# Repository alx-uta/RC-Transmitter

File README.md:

# RC-Transmitter
This is a custom RC Transmitter that's using ESP32 and Semtech SX1280

Authors:
- Marian Uta
- Alex Heisler

# Project Status - WIP
- [https://microknot.dev/rc-transmitter-project-status/](https://microknot.dev/rc-transmitter-project-status/)

---

# Useful links
- [Build Tutorial](https://microknot.dev/rc-transmitter-build-tutorial-esp32-sx1280/)
- [Wiring Tutorial](https://microknot.dev/rc-transmitter-wiring-tutorial-esp32-sx1280/)
- [Calibration Tutorial](https://microknot.dev/rc-transmitter-calibration-tutorial/)

---

- Required Parts:
  - [3D Files](https://docs.google.com/spreadsheets/d/1K6EamDLu7aNF5GFfuzi9vV8SCz_6HzOA_h1CgVDcLqo/edit?usp=sharing)
  - [PCB](https://docs.google.com/spreadsheets/d/1bTyJoKmJrHec9gnfRhsfcdIJgJ4cUt9kbDGZgcYngUU/edit?usp=sharing)
  - [BOM](https://docs.google.com/spreadsheets/d/1osKjM83mz0m_O5QN-AISYl1IssTSeUwu/edit?usp=sharing&ouid=117182597298978401444&rtpof=true&sd=true)

---
Links:
- [Discord](https://discord.gg/eHyz2aJ6)

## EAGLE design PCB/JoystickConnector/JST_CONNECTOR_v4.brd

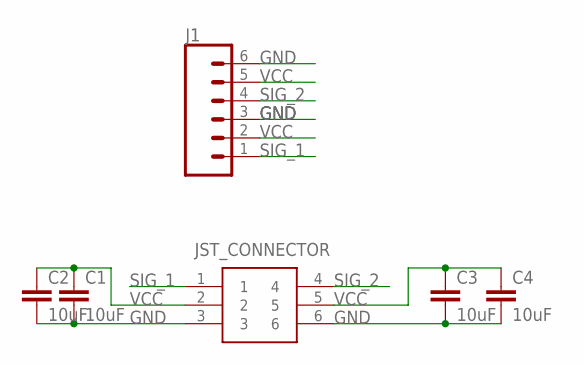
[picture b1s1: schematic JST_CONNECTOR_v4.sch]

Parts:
C1, C2, C3, C4: 10uF; 0805
J1: CONN_06SILK_FEMALE_PTH; 1X06
JST_CONNECTOR: 0532610671

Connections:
GND: C1.2, C2.2, C3.2, C4.2, J1.3, J1.6, JST_CONNECTOR.3, JST_CONNECTOR.6
SIG_1: J1.1, JST_CONNECTOR.1
SIG_2: J1.4, JST_CONNECTOR.4
VCC: C1.1, C2.1, C3.1, C4.1, J1.2, J1.5, JST_CONNECTOR.2, JST_CONNECTOR.5

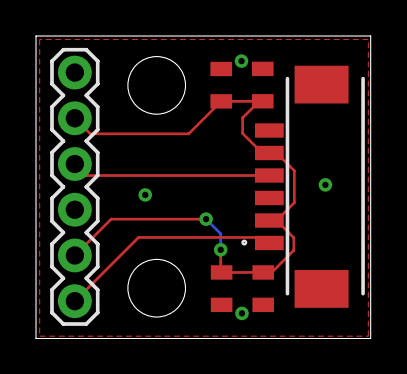
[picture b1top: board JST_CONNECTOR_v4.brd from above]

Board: 2 copper layers, 18.6 x 16.8 mm, 6 parts (0 on the bottom side), 4 nets.

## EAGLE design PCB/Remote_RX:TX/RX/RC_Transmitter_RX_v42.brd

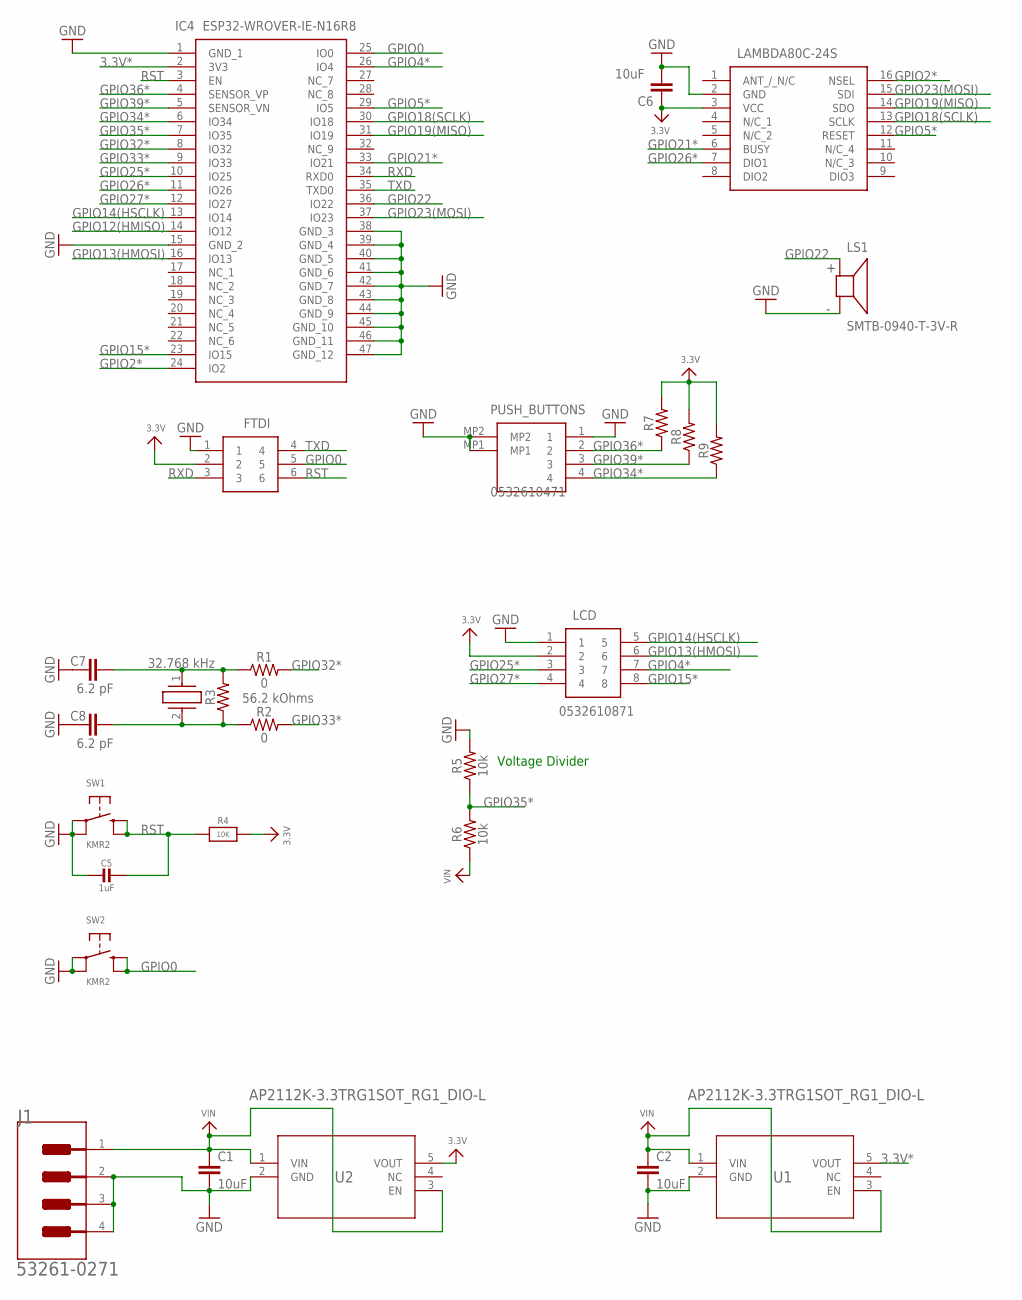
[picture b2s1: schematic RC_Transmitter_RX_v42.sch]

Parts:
C1, C2, C6: 10uF; 0805
C5: 1uF; 0805-NO
C7, C8: 6.2 pF; CAPC2012X110
CRYSTAL: 32.768 kHz; ECX327CDX1293
FTDI: 0532610671
IC1: LAMBDA80C-24S; LAMBDA80C24S
IC4: ESP32-WROVER-IE-N16R8; ESP32WROVERIEN16R8
J1: MOLEX_53261-0271MOLEX_53261-0271_0_0; MOLEX_53261-0271_0
LCD: 0532610871; 53261-0871
LS1: SMTB-0940-T-3V-R; XDCR_SMTB-0940-T-3V-R
PUSH_BUTTONS: 0532610471
R1, R2, R7, R8, R9: 0; 0603
R3: 56.2 kOhms; 0603
R4: 10K; _0805
R5, R6: 10k; 0603
SW1, SW2: KMR2; BTN_KMR2_4.6X2.8
U1, U2: AP2112K-3.3TRG1SOT_RG1_DIO-L; SOT_RG1_DIO-L

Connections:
3.3V: C6.1, FTDI.2, IC1.3 (VCC), LCD.2, R4.2, R7.2, R8.2, R9.2, U2.5 (VOUT)
3.3V*: IC4.2 (3V3), U1.5 (VOUT)
GND: C1.2, C2.2, C5.2, C6.2, C7.1, C8.1, FTDI.1, IC1.2 (GND), IC4.1 (GND_1), IC4.15 (GND_2), IC4.38 (GND_3), IC4.39 (GND_4), IC4.40 (GND_5), IC4.41 (GND_6), IC4.42 (GND_7), IC4.43 (GND_8), IC4.44 (GND_9), IC4.45 (GND_10), IC4.46 (GND_11), IC4.47 (GND_12), J1.2, J1.3 (MNT_1), J1.4 (MNT_2), LCD.1, LS1.N, PUSH_BUTTONS.1, PUSH_BUTTONS.MP1, PUSH_BUTTONS.MP2, R5.2, SW1.A, SW1.A' (P1), SW2.A, SW2.A' (P1), U1.2 (GND), U2.2 (GND)
GPIO0: FTDI.5, IC4.25 (IO0), SW2.B (S), SW2.B' (S1)
GPIO2*: IC1.16 (NSEL), IC4.24 (IO2)
GPIO4*: IC4.26 (IO4), LCD.7
GPIO5*: IC1.12 (RESET), IC4.29 (IO5)
GPIO12(HMISO): IC4.14 (IO12)
GPIO13(HMOSI): IC4.16 (IO13), LCD.6
GPIO14(HSCLK): IC4.13 (IO14), LCD.5
GPIO15*: IC4.23 (IO15), LCD.8
GPIO18(SCLK): IC1.13 (SCLK), IC4.30 (IO18)
GPIO19(MISO): IC1.14 (SDO), IC4.31 (IO19)
GPIO21*: IC1.6 (BUSY), IC4.33 (IO21)
GPIO22: IC4.36 (IO22), LS1.P
GPIO23(MOSI): IC1.15 (SDI), IC4.37 (IO23)
GPIO25*: IC4.10 (IO25), LCD.3
GPIO26*: IC1.7 (DIO1), IC4.11 (IO26)
GPIO27*: IC4.12 (IO27), LCD.4
GPIO32*: IC4.8 (IO32), R1.2
GPIO33*: IC4.9 (IO33), R2.2
GPIO34*: IC4.6 (IO34), PUSH_BUTTONS.4, R9.1
GPIO35*: IC4.7 (IO35), R5.1, R6.2
GPIO36*: IC4.4 (SENSOR_VP), PUSH_BUTTONS.2, R7.1
GPIO39*: IC4.5 (SENSOR_VN), PUSH_BUTTONS.3, R8.1
unnamed: C7.2, CRYSTAL.1 (X1), R1.1, R3.2
unnamed: C8.2, CRYSTAL.2 (X2), R2.1, R3.1
RST: C5.1, FTDI.6, IC4.3 (EN), R4.1, SW1.B (S), SW1.B' (S1)
RXD: FTDI.3, IC4.34 (RXD0)
TXD: FTDI.4, IC4.35 (TXD0)
VIN: C1.1, C2.1, J1.1, R6.1, U1.1 (VIN), U1.3 (EN), U2.1 (VIN), U2.3 (EN)

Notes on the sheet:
Voltage Divider

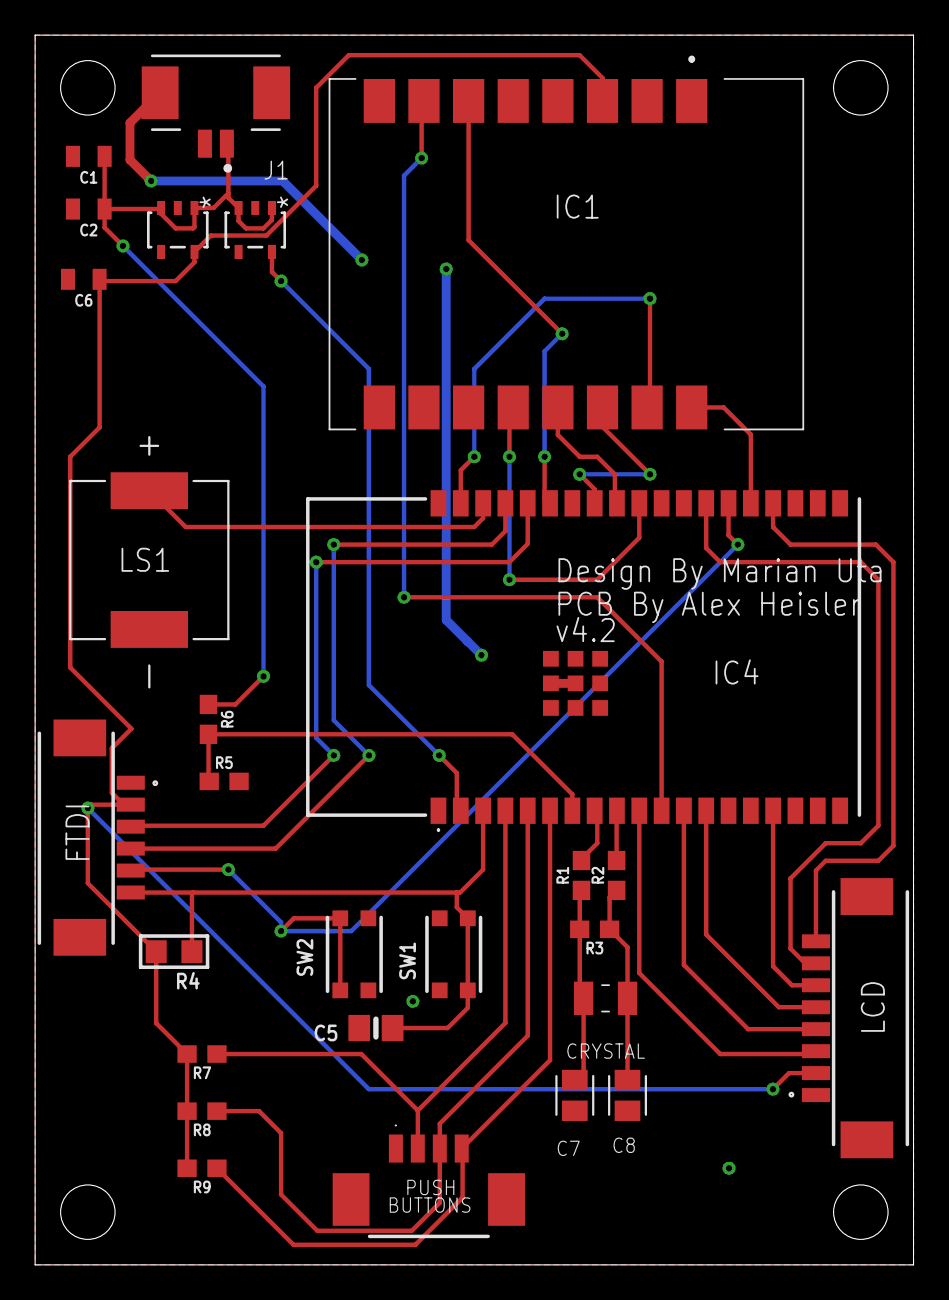
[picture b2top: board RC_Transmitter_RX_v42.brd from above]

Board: 2 copper layers, 50.0 x 70.0 mm, 27 parts (0 on the bottom side), 30 nets.

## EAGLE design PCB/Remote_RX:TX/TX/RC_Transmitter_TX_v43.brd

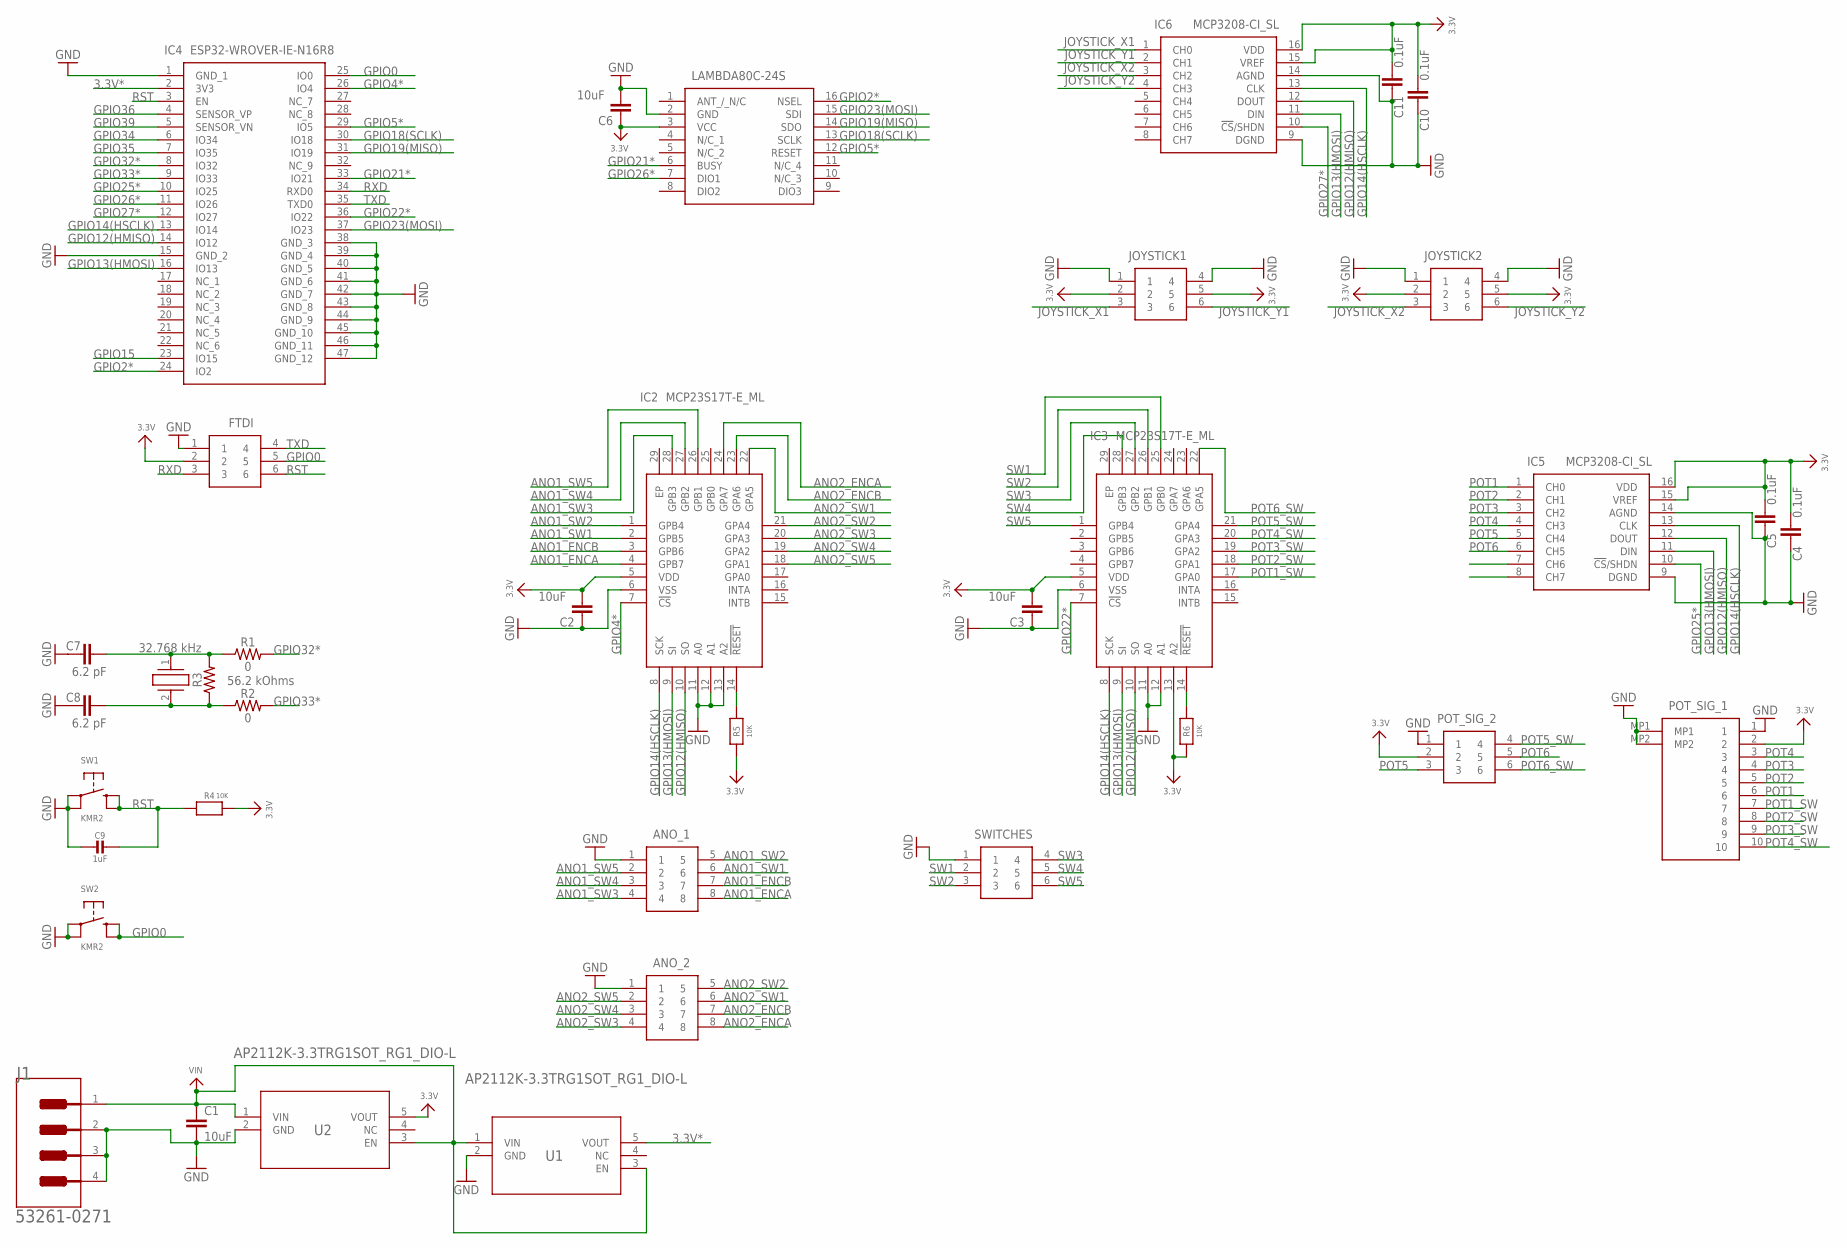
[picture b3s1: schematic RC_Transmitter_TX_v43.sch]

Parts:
ANO_1, ANO_2: 0532610871; 53261-0871
C1, C2, C3, C6: 10uF; 0805
C4, C5, C10, C11: 0.1uF; 0805
C7, C8: 6.2 pF; CAPC2012X110
C9: 1uF; 0805-NO
CRYSTAL: 32.768 kHz; ECX327CDX1293
FTDI: 0532610671
IC1: LAMBDA80C-24S; LAMBDA80C24S
IC2, IC3: MCP23S17T-E_ML; QFN65P600X600X100-29N
IC4: ESP32-WROVER-IE-N16R8; ESP32WROVERIEN16R8
IC5, IC6: MCP3208-CI_SL; SOIC127P600X175-16N
J1: MOLEX_53261-0271MOLEX_53261-0271_0_0; MOLEX_53261-0271_0
JOYSTICK1, JOYSTICK2: 0532610671
POT_SIG_1: 0532611071
POT_SIG_2: 0532610671
R1, R2: 0; 0603
R3: 56.2 kOhms; 0603
R4, R5, R6: 10K; _0805
SW1, SW2: KMR2; BTN_KMR2_4.6X2.8
SWITCHES: 0532610671
U1, U2: AP2112K-3.3TRG1SOT_RG1_DIO-L; SOT_RG1_DIO-L

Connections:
3.3V: C2.2, C3.2, C4.2, C5.2, C6.1, C10.2, C11.2, FTDI.2, IC1.3 (VCC), IC2.5 (VDD), IC3.5 (VDD), IC3.13 (A2), IC5.15 (VREF), IC5.16 (VDD), IC6.15 (VREF), IC6.16 (VDD), JOYSTICK1.2, JOYSTICK1.5, JOYSTICK2.2, JOYSTICK2.5, POT_SIG_1.2, POT_SIG_2.2, R4.2, R5.1, R6.1, U2.5 (VOUT)
3.3V*: IC4.2 (3V3), U1.5 (VOUT)
ANO1_ENCA: ANO_1.8, IC2.4 (GPB7)
ANO1_ENCB: ANO_1.7, IC2.3 (GPB6)
ANO1_SW1: ANO_1.6, IC2.2 (GPB5)
ANO1_SW2: ANO_1.5, IC2.1 (GPB4)
ANO1_SW3: ANO_1.4, IC2.28 (GPB3)
ANO1_SW4: ANO_1.3, IC2.27 (GPB2)
ANO1_SW5: ANO_1.2, IC2.26 (GPB1)
ANO2_ENCA: ANO_2.8, IC2.24 (GPA7)
ANO2_ENCB: ANO_2.7, IC2.23 (GPA6)
ANO2_SW1: ANO_2.6, IC2.22 (GPA5)
ANO2_SW2: ANO_2.5, IC2.21 (GPA4)
ANO2_SW3: ANO_2.4, IC2.20 (GPA3)
ANO2_SW4: ANO_2.3, IC2.19 (GPA2)
ANO2_SW5: ANO_2.2, IC2.18 (GPA1)
GND: ANO_1.1, ANO_2.1, C1.2, C2.1, C3.1, C4.1, C5.1, C6.2, C7.1, C8.1, C9.2, C10.1, C11.1, FTDI.1, IC1.2 (GND), IC2.6 (VSS), IC2.11 (A0), IC2.12 (A1), IC2.13 (A2), IC3.6 (VSS), IC3.11 (A0), IC3.12 (A1), IC4.1 (GND_1), IC4.15 (GND_2), IC4.38 (GND_3), IC4.39 (GND_4), IC4.40 (GND_5), IC4.41 (GND_6), IC4.42 (GND_7), IC4.43 (GND_8), IC4.44 (GND_9), IC4.45 (GND_10), IC4.46 (GND_11), IC4.47 (GND_12), IC5.9 (DGND), IC5.14 (AGND), IC6.9 (DGND), IC6.14 (AGND), J1.2, J1.3 (MNT_1), J1.4 (MNT_2), JOYSTICK1.1, JOYSTICK1.4, JOYSTICK2.1, JOYSTICK2.4, POT_SIG_1.1, POT_SIG_1.MP1, POT_SIG_1.MP2, POT_SIG_2.1, SW1.A, SW1.A' (P1), SW2.A, SW2.A' (P1), SWITCHES.1, U1.2 (GND), U2.2 (GND)
GPIO0: FTDI.5, IC4.25 (IO0), SW2.B (S), SW2.B' (S1)
GPIO2*: IC1.16 (NSEL), IC4.24 (IO2)
GPIO4*: IC2.7 (!CS), IC4.26 (IO4)
GPIO5*: IC1.12 (RESET), IC4.29 (IO5)
GPIO12(HMISO): IC2.10 (SO), IC3.10 (SO), IC4.14 (IO12), IC5.12 (DOUT), IC6.12 (DOUT)
GPIO13(HMOSI): IC2.9 (SI), IC3.9 (SI), IC4.16 (IO13), IC5.11 (DIN), IC6.11 (DIN)
GPIO14(HSCLK): IC2.8 (SCK), IC3.8 (SCK), IC4.13 (IO14), IC5.13 (CLK), IC6.13 (CLK)
GPIO15: IC4.23 (IO15)
GPIO18(SCLK): IC1.13 (SCLK), IC4.30 (IO18)
GPIO19(MISO): IC1.14 (SDO), IC4.31 (IO19)
GPIO21*: IC1.6 (BUSY), IC4.33 (IO21)
GPIO22*: IC3.7 (!CS), IC4.36 (IO22)
GPIO23(MOSI): IC1.15 (SDI), IC4.37 (IO23)
GPIO25*: IC4.10 (IO25), IC5.10 (!CS!/SHDN)
GPIO26*: IC1.7 (DIO1), IC4.11 (IO26)
GPIO27*: IC4.12 (IO27), IC6.10 (!CS!/SHDN)
GPIO32*: IC4.8 (IO32), R1.2
GPIO33*: IC4.9 (IO33), R2.2
GPIO34: IC4.6 (IO34)
GPIO35: IC4.7 (IO35)
GPIO36: IC4.4 (SENSOR_VP)
GPIO39: IC4.5 (SENSOR_VN)
JOYSTICK_X1: IC6.1 (CH0), JOYSTICK1.3
JOYSTICK_X2: IC6.3 (CH2), JOYSTICK2.3
JOYSTICK_Y1: IC6.2 (CH1), JOYSTICK1.6
JOYSTICK_Y2: IC6.4 (CH3), JOYSTICK2.6
unnamed: C7.2, CRYSTAL.1 (X1), R1.1, R3.2
unnamed: C8.2, CRYSTAL.2 (X2), R2.1, R3.1
unnamed: IC2.14 (!RESET), R5.2
unnamed: IC3.14 (!RESET), R6.2
POT1: IC5.1 (CH0), POT_SIG_1.6
POT1_SW: IC3.17 (GPA0), POT_SIG_1.7
POT2: IC5.2 (CH1), POT_SIG_1.5
POT2_SW: IC3.18 (GPA1), POT_SIG_1.8
POT3: IC5.3 (CH2), POT_SIG_1.4
POT3_SW: IC3.19 (GPA2), POT_SIG_1.9
POT4: IC5.4 (CH3), POT_SIG_1.3
POT4_SW: IC3.20 (GPA3), POT_SIG_1.10
POT5: IC5.5 (CH4), POT_SIG_2.3
POT5_SW: IC3.21 (GPA4), POT_SIG_2.4
POT6: IC5.6 (CH5), POT_SIG_2.5
POT6_SW: IC3.22 (GPA5), POT_SIG_2.6
RST: C9.1, FTDI.6, IC4.3 (EN), R4.1, SW1.B (S), SW1.B' (S1)
RXD: FTDI.3, IC4.34 (RXD0)
SW1: IC3.25 (GPB0), SWITCHES.2
SW2: IC3.26 (GPB1), SWITCHES.3
SW3: IC3.27 (GPB2), SWITCHES.4
SW4: IC3.28 (GPB3), SWITCHES.5
SW5: IC3.1 (GPB4), SWITCHES.6
TXD: FTDI.4, IC4.35 (TXD0)
VIN: C1.1, J1.1, U1.1 (VIN), U1.3 (EN), U2.1 (VIN), U2.3 (EN)

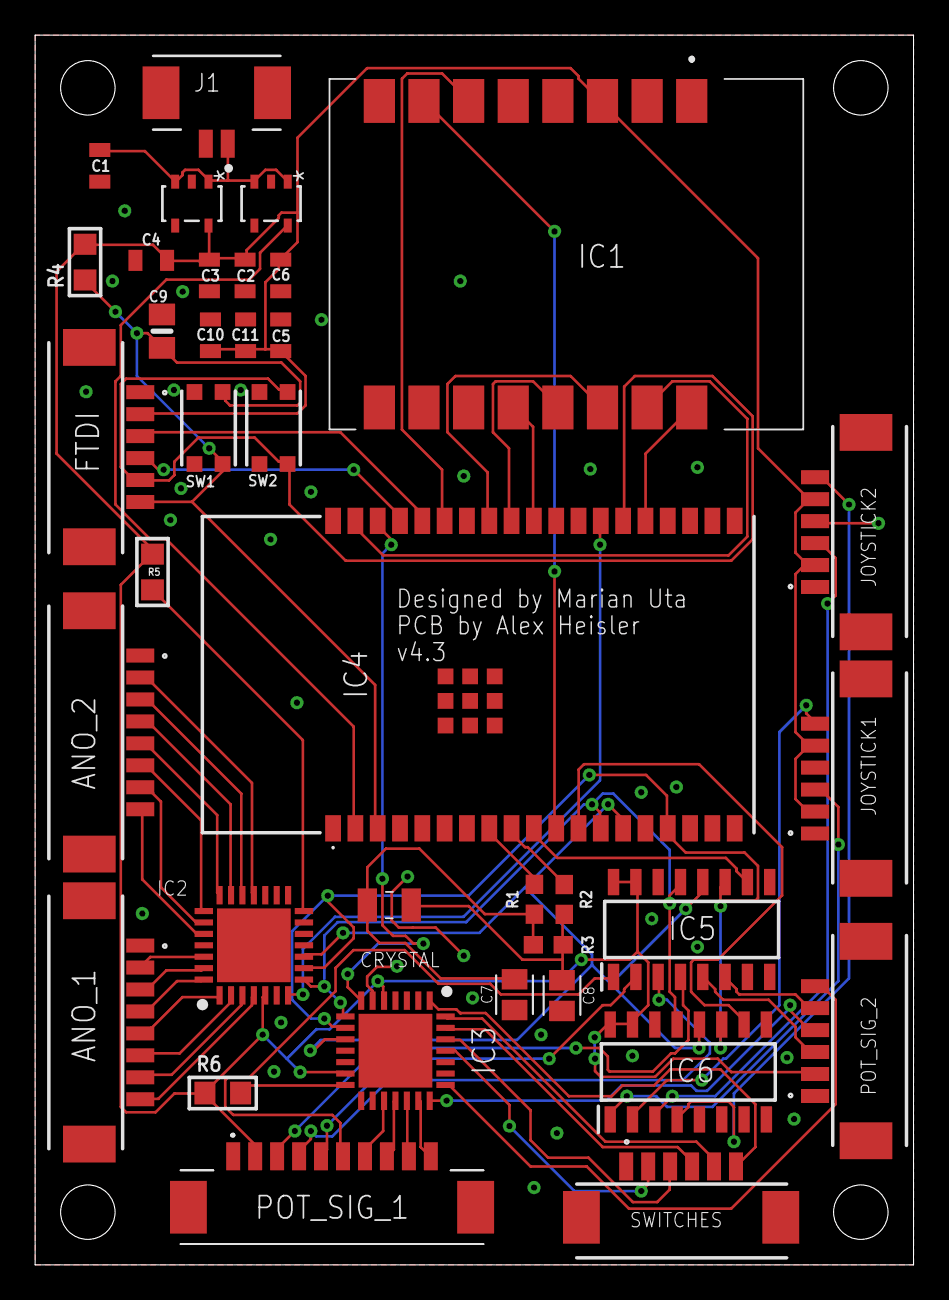
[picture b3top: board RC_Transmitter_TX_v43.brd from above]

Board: 2 copper layers, 50.0 x 70.0 mm, 37 parts (0 on the bottom side), 63 nets.

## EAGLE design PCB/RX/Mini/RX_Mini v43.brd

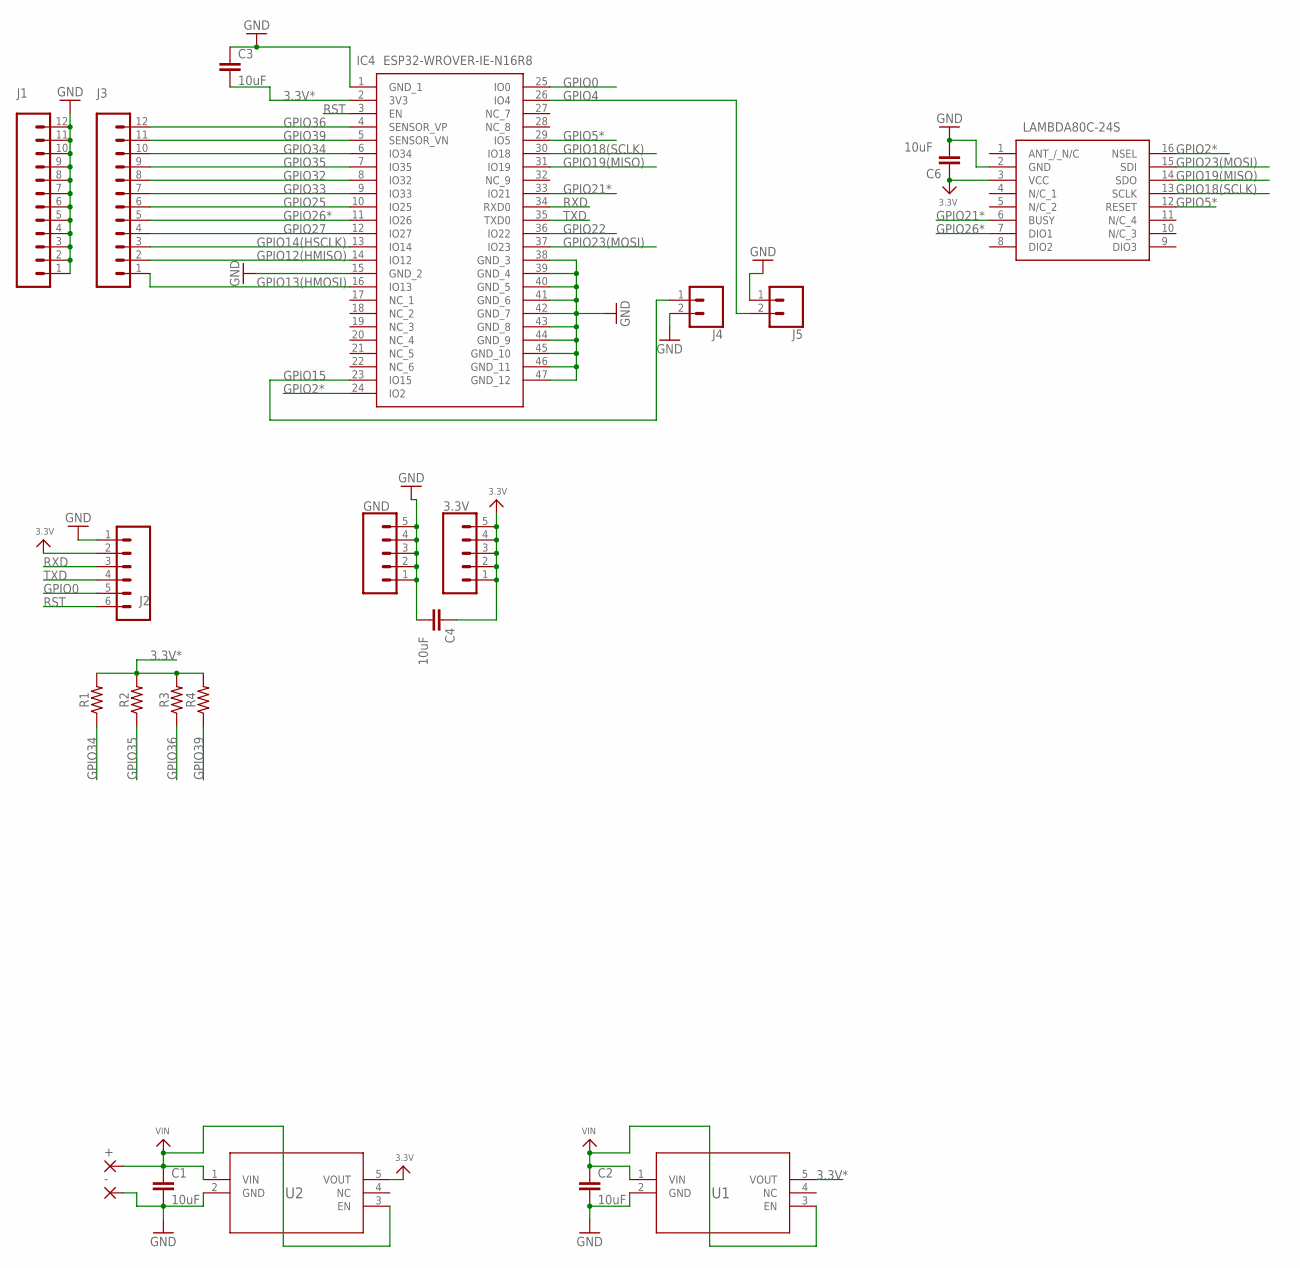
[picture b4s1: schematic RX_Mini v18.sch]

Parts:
3.3V: CONN_05; 1X05
+: 2,15/1,0
-: 2,15/1,0
C1, C2, C3, C4, C6: 10uF; 0805
GND: CONN_05; 1X05
IC1: LAMBDA80C-24S; LAMBDA80C24S
IC4: ESP32-WROVER-IE-N16R8; ESP32WROVERIEN16R8
J1, J3: CONN_12; 1X12
J2: CONN_06NO_SILK_NO_POP; 1X06_NO_SILK
J4, J5: CONN_02; 1X02
R1, R2, R3, R4: 0; 0603
U1, U2: AP2112K-3.3TRG1SOT_RG1_DIO-L; SOT_RG1_DIO-L

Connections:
3.3V: 3.3V.1, 3.3V.2, 3.3V.3, 3.3V.4, 3.3V.5, C4.1, C6.1, IC1.3 (VCC), J2.2, U2.5 (VOUT)
3.3V*: C3.2, IC4.2 (3V3), R1.2, R2.2, R3.2, R4.2, U1.5 (VOUT)
GND: -.1, C1.2, C2.2, C3.1, C4.2, C6.2, GND.1, GND.2, GND.3, GND.4, GND.5, IC1.2 (GND), IC4.1 (GND_1), IC4.15 (GND_2), IC4.38 (GND_3), IC4.39 (GND_4), IC4.40 (GND_5), IC4.41 (GND_6), IC4.42 (GND_7), IC4.43 (GND_8), IC4.44 (GND_9), IC4.45 (GND_10), IC4.46 (GND_11), IC4.47 (GND_12), J1.1, J1.2, J1.3, J1.4, J1.5, J1.6, J1.7, J1.8, J1.9, J1.10, J1.11, J1.12, J2.1, J4.2, J5.1, U1.2 (GND), U2.2 (GND)
GPIO0: IC4.25 (IO0), J2.5
GPIO2*: IC1.16 (NSEL), IC4.24 (IO2)
GPIO4: IC4.26 (IO4), J5.2
GPIO5*: IC1.12 (RESET), IC4.29 (IO5)
GPIO12(HMISO): IC4.14 (IO12), J3.2
GPIO13(HMOSI): IC4.16 (IO13), J3.1
GPIO14(HSCLK): IC4.13 (IO14), J3.3
GPIO15: IC4.23 (IO15), J4.1
GPIO18(SCLK): IC1.13 (SCLK), IC4.30 (IO18)
GPIO19(MISO): IC1.14 (SDO), IC4.31 (IO19)
GPIO21*: IC1.6 (BUSY), IC4.33 (IO21)
GPIO22: IC4.36 (IO22)
GPIO23(MOSI): IC1.15 (SDI), IC4.37 (IO23)
GPIO25: IC4.10 (IO25), J3.6
GPIO26*: IC1.7 (DIO1), IC4.11 (IO26), J3.5
GPIO27: IC4.12 (IO27), J3.4
GPIO32: IC4.8 (IO32), J3.8
GPIO33: IC4.9 (IO33), J3.7
GPIO34: IC4.6 (IO34), J3.10, R1.1
GPIO35: IC4.7 (IO35), J3.9, R2.1
GPIO36: IC4.4 (SENSOR_VP), J3.12, R3.1
GPIO39: IC4.5 (SENSOR_VN), J3.11, R4.1
RST: IC4.3 (EN), J2.6
RXD: IC4.34 (RXD0), J2.3
TXD: IC4.35 (TXD0), J2.4
VIN: +.1, C1.1, C2.1, U1.1 (VIN), U1.3 (EN), U2.1 (VIN), U2.3 (EN)

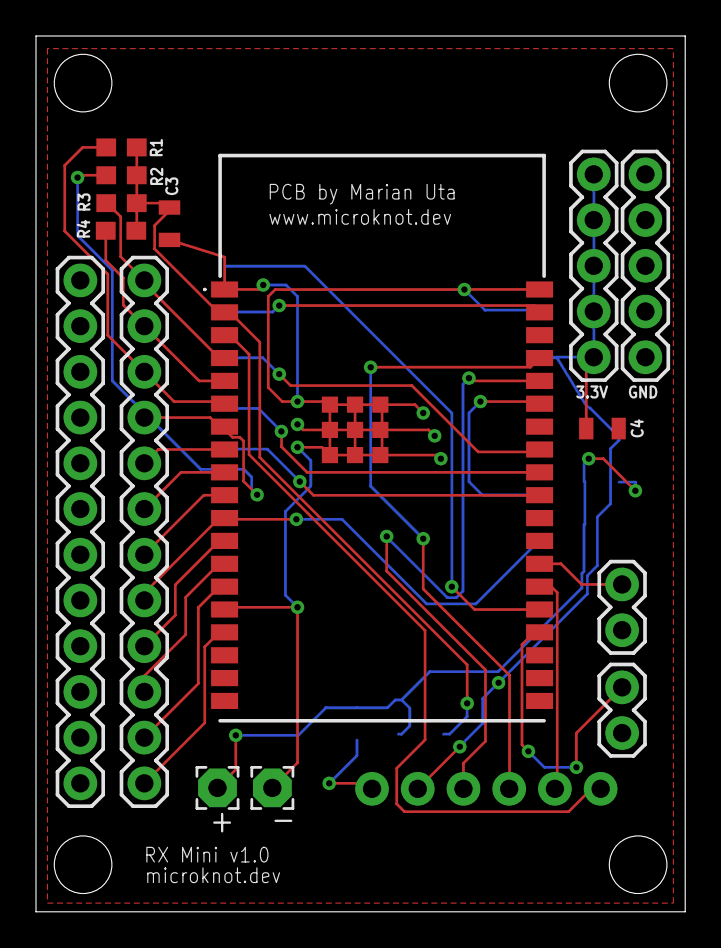
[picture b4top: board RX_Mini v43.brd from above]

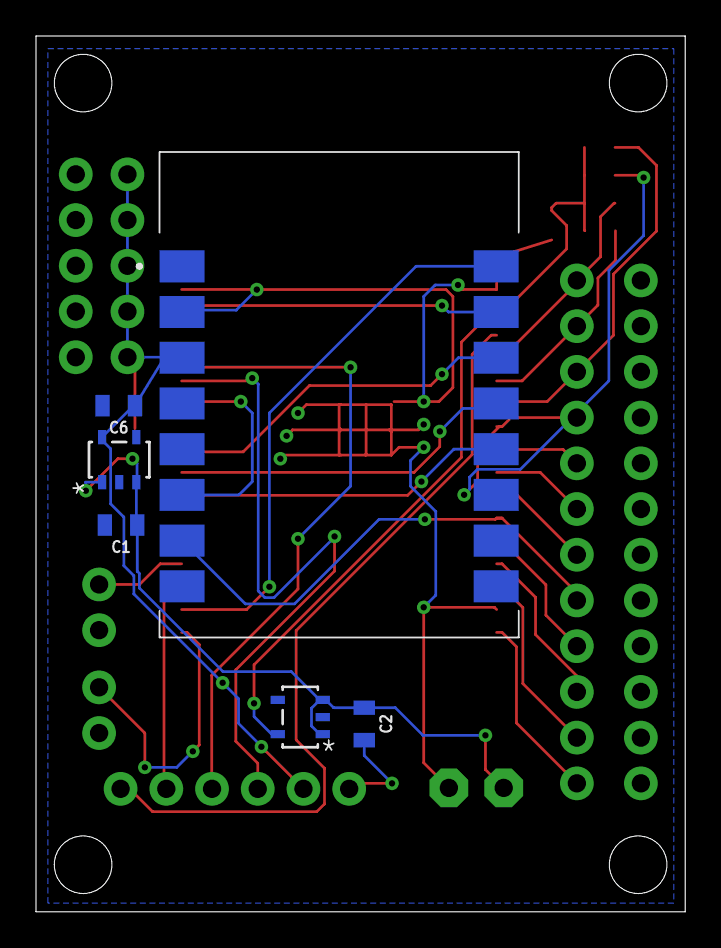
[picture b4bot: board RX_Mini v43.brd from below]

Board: 2 copper layers, 36.1 x 48.7 mm, 22 parts (6 on the bottom side), 28 nets.

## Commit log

2023-07-17 3D Files
2023-07-17 Spacer Removed - Not needed
2023-07-17 Fixed the battery holder
2023-08-08 STP/STEP files update
2023-08-09 code backup
2023-08-09 config - removed
2023-08-09 file remove.
2023-08-09 gitignore update
2023-08-09 TX Code beta-1.0
    * code backup
    * code backup
    * code backup
    * Update config.h
    * config - removed
    * code backup
2023-08-10 TX_Calibration beta-1.0
2023-08-10 TX_Calibration beta-1.0 (#3)
2023-08-19 Remote TX code improvements
2023-08-19 Remote TX code improvements (#4)
2023-09-05 TX Improvements
2023-09-05 Code Improvements (#5)
2023-09-07 Remote RX - PCB Update
2023-09-16 Remote RX Receiver & Remote TX Improvements
2023-09-16 Remote RX Receiver & Remote TX Improvements (#6)
2023-09-17 Reduce the Payload from 21 to 17
2023-10-17 Code Improvements
2023-10-17 PCB Update
2023-10-17 Battery Widget Bug Fix
2023-10-17 Transmitter Improvements (#7)
    * Code Improvements
    * PCB Update
    * Battery Widget Bug Fix
2023-10-29 Code Update
2024-01-06 RC Transmitter
2024-01-06 Code Improvements (#9)
2024-04-09 FLRC
2025-04-07 fix windows path
2025-04-07 Directory Rename

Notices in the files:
parts and their libraries:
SparkFun-Connectors: Licensing: Creative Commons ShareAlike 4.0 International - https://creativecommons.org/licenses/by-sa/4.0
microbuilder: This work is placed in the public domain, and may be freely used for commercial and non-commercial work with the following conditions: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
